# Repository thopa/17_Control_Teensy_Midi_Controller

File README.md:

# 17_Control_Teensy_Midi_Controller
Teensy based midi controller inspired by the monome Fourn and Arc

When downloading and extracting files, make sure name.h is in the same folder as the 17_Teensy_Midi_Controller.ino

Arduino does not keep the same file estructure when extracting.

Bill of Materials:

*Teensy 3.2

*ALPHA VERTICAL 9MM POTENTIOMETER (tested with 25k&10k)
https://www.thonk.co.uk/shop/alpha-9mm-pots/

*Knobs & Caps:

Black Small Skirt D - Sifam Plastic Knob
https://www.thonk.co.uk/shop/intellijel-black-knobs/

Small Grey - Sifam Plastic Cap
https://www.thonk.co.uk/shop/sifam-caps/

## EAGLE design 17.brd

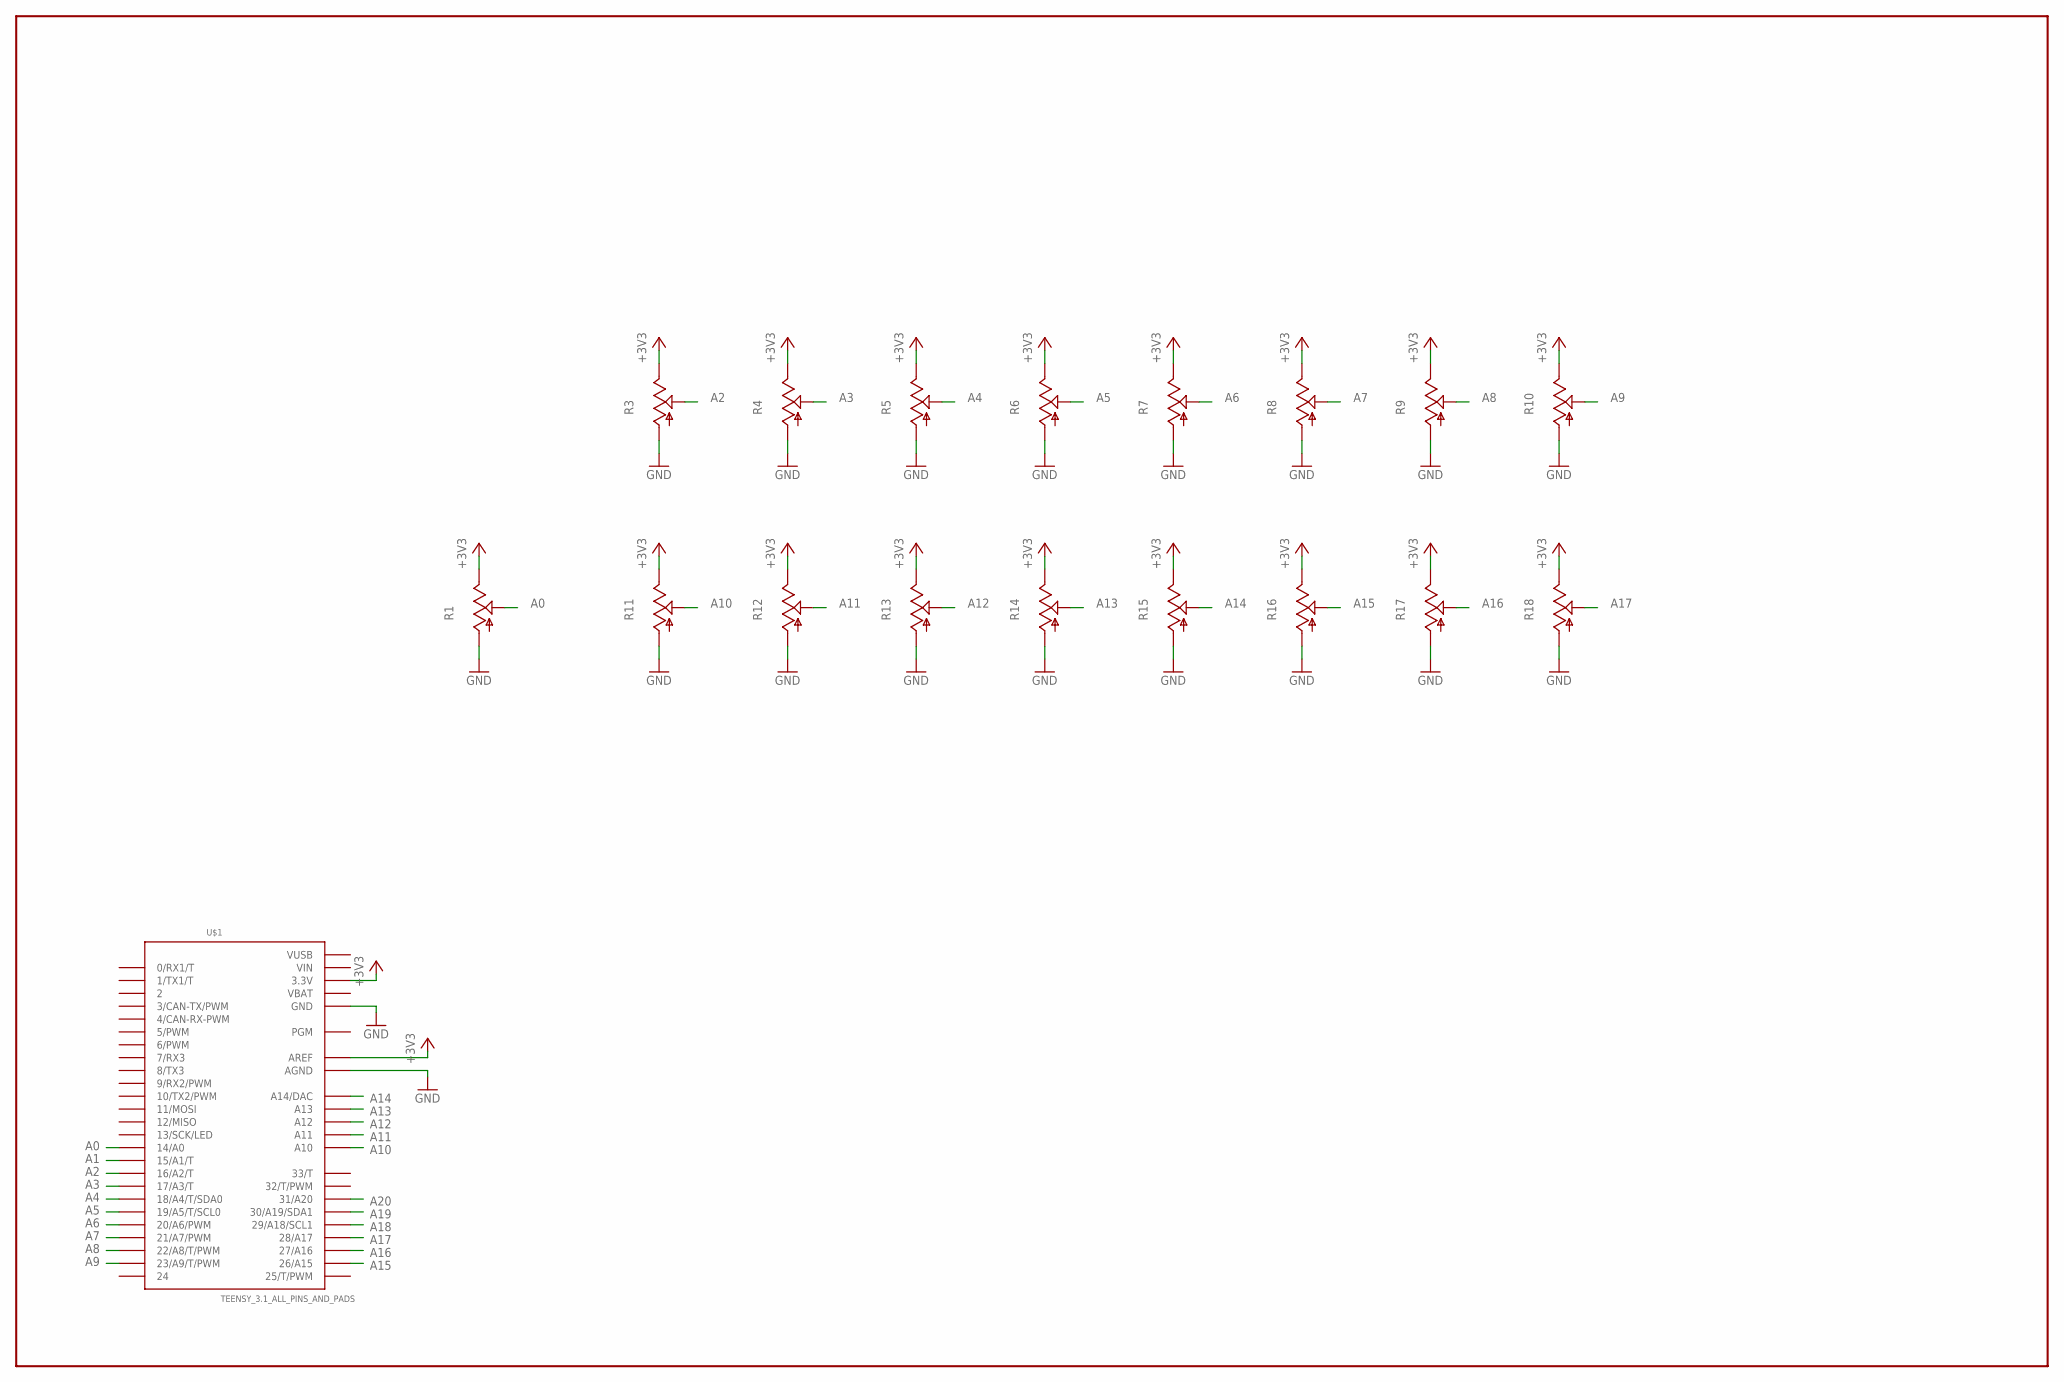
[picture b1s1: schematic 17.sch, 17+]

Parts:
R1, R3, R4, R5, R6, R7, R8, R9, R10, R11, R12, R13, R14, R15, R16, R17, R18: SHAPES_POT-ALPS_POT_USVERTICAL_PS; SHAPES_POT-ALPS_ALPS_POT_VERTICAL_PS
U$1: TEENSY_3.1_ALL_PINS_AND_PADS; TEENSY_3.1_ALLPINS

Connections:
+3V3: R1.P$1 (E), R3.P$1 (E), R4.P$1 (E), R5.P$1 (E), R6.P$1 (E), R7.P$1 (E), R8.P$1 (E), R9.P$1 (E), R10.P$1 (E), R11.P$1 (E), R12.P$1 (E), R13.P$1 (E), R14.P$1 (E), R15.P$1 (E), R16.P$1 (E), R17.P$1 (E), R18.P$1 (E), U$1.3.3V, U$1.3.3V1 (3.3V), U$1.3.3V2 (3.3V), U$1.AREF
A0: R1.P$2 (S), U$1.14/A0
A1: U$1.15/A1 (15/A1/T)
A2: R3.P$2 (S), U$1.16/A2 (16/A2/T)
A3: R4.P$2 (S), U$1.17/A3 (17/A3/T)
A4: R5.P$2 (S), U$1.18/A4 (18/A4/T/SDA0)
A5: R6.P$2 (S), U$1.19/A5 (19/A5/T/SCL0)
A6: R7.P$2 (S), U$1.20/A6 (20/A6/PWM)
A7: R8.P$2 (S), U$1.21/A7 (21/A7/PWM)
A8: R9.P$2 (S), U$1.22/A8 (22/A8/T/PWM)
A9: R10.P$2 (S), U$1.23/A9 (23/A9/T/PWM)
A10: R11.P$2 (S), U$1.A10
A11: R12.P$2 (S), U$1.A11
A12: R13.P$2 (S), U$1.A12
A13: R14.P$2 (S), U$1.A13
A14: R15.P$2 (S), U$1.A14 (A14/DAC)
A15: R16.P$2 (S), U$1.26 (26/A15)
A16: R17.P$2 (S), U$1.27 (27/A16)
A17: R18.P$2 (S), U$1.28 (28/A17)
A18: U$1.29 (29/A18/SCL1)
A19: U$1.30 (30/A19/SDA1)
A20: U$1.31 (31/A20)
GND: R1.P$3 (A), R3.P$3 (A), R4.P$3 (A), R5.P$3 (A), R6.P$3 (A), R7.P$3 (A), R8.P$3 (A), R9.P$3 (A), R10.P$3 (A), R11.P$3 (A), R12.P$3 (A), R13.P$3 (A), R14.P$3 (A), R15.P$3 (A), R16.P$3 (A), R17.P$3 (A), R18.P$3 (A), U$1.AGND, U$1.GND, U$1.GND1 (GND), U$1.GND2 (GND)
VBAT: U$1.VBAT
VIN: U$1.VIN
VUSB: U$1.VUSB

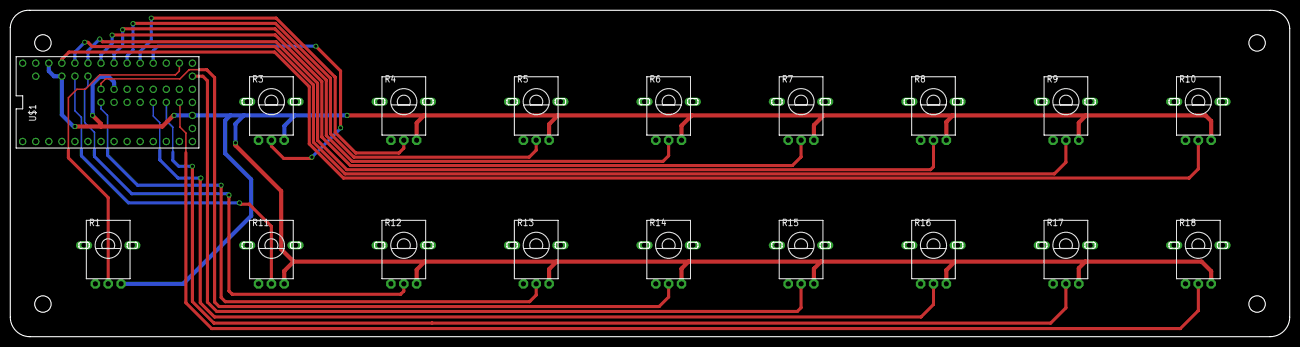
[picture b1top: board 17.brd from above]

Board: 2 copper layers, 248.9 x 63.5 mm, 18 parts (0 on the bottom side), 19 nets.

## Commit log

2020-01-16 Rename 17+.sch to 17.sch
2020-01-16 Rename 17+.brd to 17.brd
2020-01-16 Rename panel_final_a12_p3.svg to Top_Bottom_Laser_Razorlab.svg
2020-01-16 Create Firmware
